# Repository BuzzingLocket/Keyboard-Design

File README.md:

# May 8th 2026 Initial Release 🚀
- 80% keyboard ansi
- Missing a ctrl key on the righthand side
- Uses a Raspberry Pi Pico as the MCU, I was too lazy to implement my own rp2040 MCU design
- Firmware will be updated at a later date
- Everything is designed to be hand soldered
- Printed using a lpkf protomat s103 with traces at 0.4mm, and vias at 0.6mm

# May 14th 2026 Hotfix 🛠️
- lpkf protomat s103 requires vias at 0.8mm diameter with a hole of 0.4mm
- Not the same as 0.6mm diameter with a hole of 0.3mm
- Decided to print with JLCPCB instead of school PCB printer due to costs

# June 2nd 2026 Firmware Release 🚀
- Added QMK firmware
- Full matrix finished
- RGB added
- Could be errors, requires more testing
- QMK uses HSV (hue, saturation, value) not RGB (Red, Green, Blue)

# June 14th 2026 Firmware Update ⚡
- Finalized the QMK firmware
- Edited the rotary encoder resolution from 2 --> 4
- Switched GP21 and GP20 due to preference
- Finished testing keyboard
- Uploaded as .c file

# June 20th 2026 Case Design Release 🚀
- Learned how to use Fusion360
- Created bottom case housing
- Pillars for M2 screws and for support
- 4mm base depth
- 5mm wide walls
- 6mm pillars for pcb to lie on-top
- Designed for M2x4mm (3.5mm width) heat inserts
- Designed for M2x5mm screws
- Uploaded as .STEP and .STL

# June 20th 2026 Firmware Quality of Life ✨
- Uploaded .uf2 file for firmware
- Renamed folders for recognition
- Removed USB C datasheet as it was not used

# August 7th 2026 Keyboard Case Update⚡
- Had to go do some tasks for work so I could not update this for a while
- Went on vacation so long break was taken
- Old keyboard design was not accurate Ie. sides were 5.231mm not 5mm
- Added 1mm tolerance to each edge
- Added holes into the walls
  - Allows for a top portion of the case
      - Higher case level
      - Covers the exposed microcontroller
   
# August 9th 2026 Keyboard Case Update⚡
- Uploaded top case files .stl and .step
- Started the top case design
- Added pillars to insert into sockets from the bottom case
- Added a cover for the Pi Pico

# August 15th 2026 Keyboard Case Update⚡
- Updated bot case files .stl and .step
- Holes were too small as they shrunk when cooled
  - Expanded hole radius by 0.25mm
- Cover for pi pico on 1top case is accurate

# August 25th 2026 Keyboard Print Files Update⚡
- Finished certification and testing of all cases
- Purchasing filament
- Printing at Toronto Metropolitan Universities DME

# September 3rd 2026 Keyboard Print Files Update⚡
- Updated Keyboard print files
- Added a fin onto the back of the Bot_Case to make it print more stable
- Fin helps print diagonally without excessive use of filament from auto generated supports

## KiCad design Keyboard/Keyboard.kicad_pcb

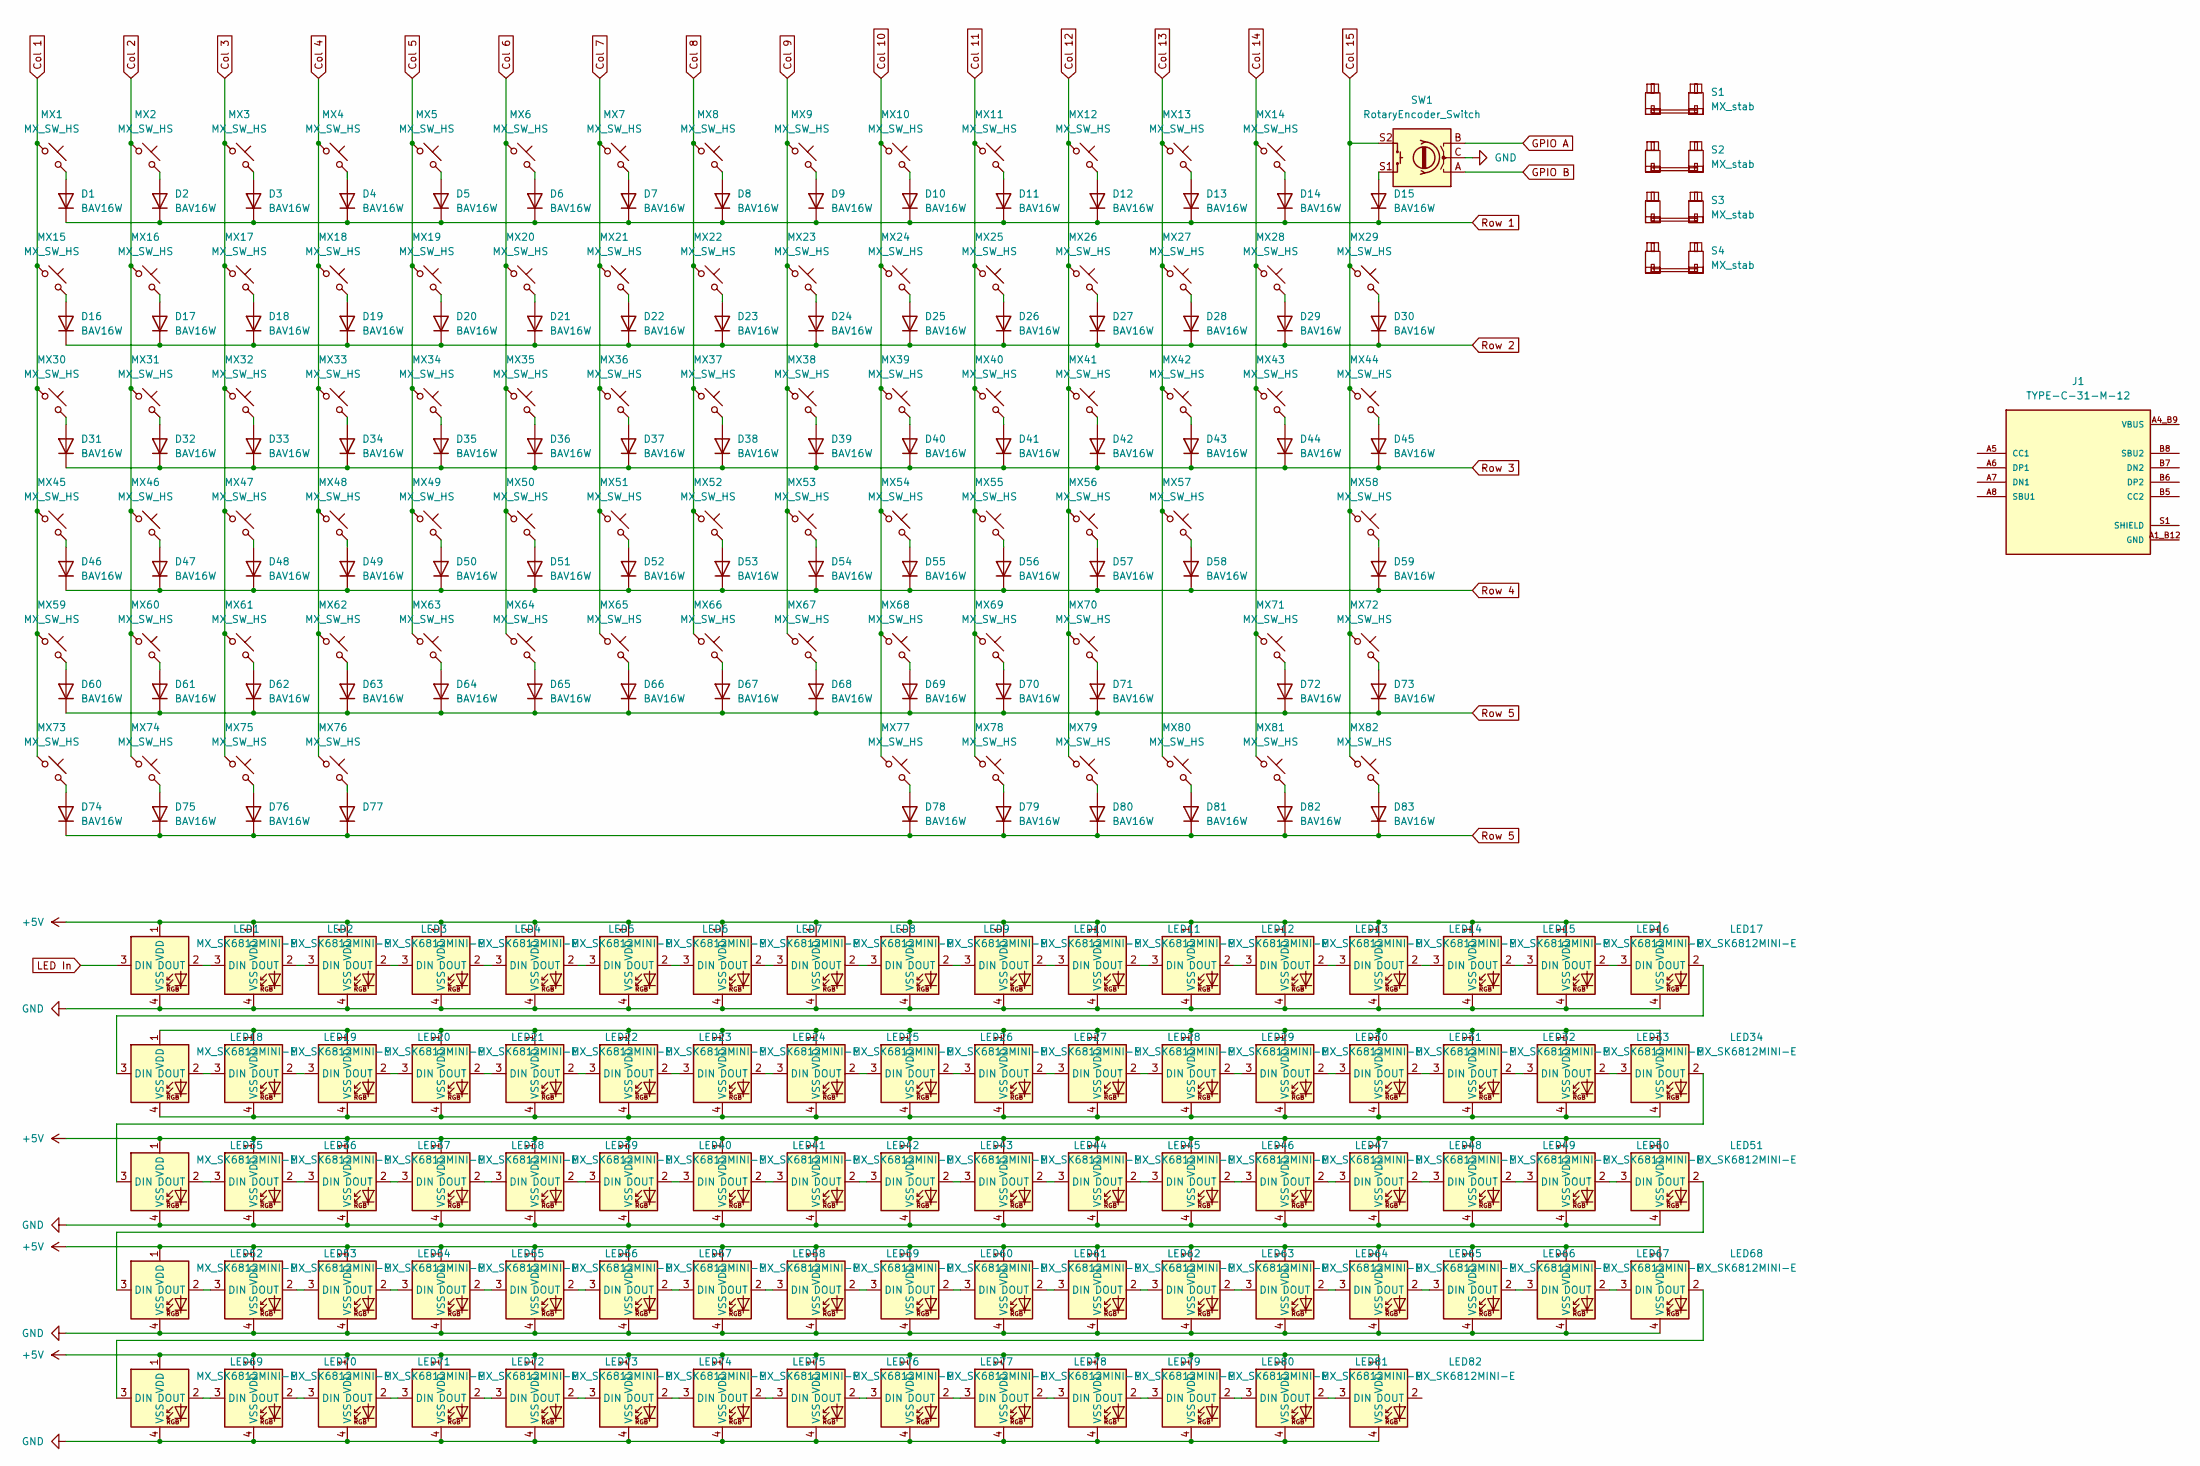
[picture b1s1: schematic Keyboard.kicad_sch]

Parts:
D1, D2, D3, D4, D5, D6, D7, D8, D9, D10, D11, D12, D13, D14, D15, D16, D17, D18, D19, D20, D21, D22, D23, D24, D25, D26, D27, D28, D29, D30, D31, D32, D33, D34, D35, D36, D37, D38, D39, D40, D41, D42, D43, D44, D45, D46, D47, D48, D49, D50, D51, D52, D53, D54, D55, D56, D57, D58, D59, D60, D61, D62, D63, D64, D65, D66, D67, D68, D69, D70, D71, D72, D73, D74, D75, D76, D77, D78, D79, D80, D81, D82, D83: BAV16W; D_SOD-123
J1: TYPE-C-31-M-12; HRO_TYPE-C-31-M-12
LED1, LED2, LED3, LED4, LED5, LED6, LED7, LED8, LED9, LED10, LED11, LED12, LED13, LED14, LED15, LED16, LED17, LED18, LED19, LED20, LED21, LED22, LED23, LED24, LED25, LED26, LED27, LED28, LED29, LED30, LED31, LED32, LED33, LED34, LED35, LED36, LED37, LED38, LED39, LED40, LED41, LED42, LED43, LED44, LED45, LED46, LED47, LED48, LED49, LED50, LED51, LED52, LED53, LED54, LED55, LED56, LED57, LED58, LED59, LED60, LED61, LED62, LED63, LED64, LED65, LED66, LED67, LED68, LED69, LED70, LED71, LED72, LED73, LED74, LED75, LED76, LED77, LED78, LED79, LED80, LED81, LED82: MX_SK6812MINI-E; LED_MX_6028R
MX1, MX2, MX3, MX4, MX5, MX6, MX7, MX8, MX9, MX10, MX11, MX12, MX13, MX14, MX15, MX16, MX17, MX18, MX19, MX20, MX21, MX22, MX23, MX24, MX25, MX26, MX27, MX28, MX29, MX31, MX32, MX33, MX34, MX35, MX36, MX37, MX38, MX39, MX40, MX41, MX42, MX44, MX46, MX47, MX48, MX49, MX50, MX51, MX52, MX53, MX54, MX55, MX56, MX57, MX58, MX59, MX60, MX61, MX62, MX63, MX64, MX65, MX66, MX67, MX68, MX69, MX71, MX72, MX76, MX77, MX78, MX79, MX80, MX81, MX82: MX_SW_HS; SW_MX_HS_CPG151101S11_1u
MX30, MX43: MX_SW_HS; SW_MX_HS_CPG151101S11_1.5u
MX45, MX70: MX_SW_HS; SW_MX_HS_CPG151101S11_1.75u
MX73, MX74, MX75: MX_SW_HS; SW_MX_HS_CPG151101S11_1.25u
S1: MX_stab; STAB_MX_P_2u
S2, S3: MX_stab; STAB_MX_P_2.25u
S4: MX_stab; STAB_MX_P_6.25u
SW1: RotaryEncoder_Switch; RotaryEncoder_Alps_EC11E-Switch_Vertical_H20mm

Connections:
+5V: LED1.1 (VDD), LED2.1 (VDD), LED3.1 (VDD), LED4.1 (VDD), LED5.1 (VDD), LED6.1 (VDD), LED7.1 (VDD), LED8.1 (VDD), LED9.1 (VDD), LED10.1 (VDD), LED11.1 (VDD), LED12.1 (VDD), LED13.1 (VDD), LED14.1 (VDD), LED15.1 (VDD), LED16.1 (VDD), LED17.1 (VDD), LED35.1 (VDD), LED36.1 (VDD), LED37.1 (VDD), LED38.1 (VDD), LED39.1 (VDD), LED40.1 (VDD), LED41.1 (VDD), LED42.1 (VDD), LED43.1 (VDD), LED44.1 (VDD), LED45.1 (VDD), LED46.1 (VDD), LED47.1 (VDD), LED48.1 (VDD), LED49.1 (VDD), LED50.1 (VDD), LED51.1 (VDD), LED52.1 (VDD), LED53.1 (VDD), LED54.1 (VDD), LED55.1 (VDD), LED56.1 (VDD), LED57.1 (VDD), LED58.1 (VDD), LED59.1 (VDD), LED60.1 (VDD), LED61.1 (VDD), LED62.1 (VDD), LED63.1 (VDD), LED64.1 (VDD), LED65.1 (VDD), LED66.1 (VDD), LED67.1 (VDD), LED68.1 (VDD), LED69.1 (VDD), LED70.1 (VDD), LED71.1 (VDD), LED72.1 (VDD), LED73.1 (VDD), LED74.1 (VDD), LED75.1 (VDD), LED76.1 (VDD), LED77.1 (VDD), LED78.1 (VDD), LED79.1 (VDD), LED80.1 (VDD), LED81.1 (VDD), LED82.1 (VDD)
Col 1: MX1.1, MX15.1, MX30.1, MX45.1, MX59.1, MX73.1
Col 2: MX2.1, MX16.1, MX31.1, MX46.1, MX60.1, MX74.1
Col 3: MX3.1, MX17.1, MX32.1, MX47.1, MX61.1, MX75.1
Col 4: MX4.1, MX18.1, MX33.1, MX48.1, MX62.1, MX76.1
Col 5: MX5.1, MX19.1, MX34.1, MX49.1, MX63.1
Col 6: MX6.1, MX20.1, MX35.1, MX50.1, MX64.1
Col 7: MX7.1, MX21.1, MX36.1, MX51.1, MX65.1
Col 8: MX8.1, MX22.1, MX37.1, MX52.1, MX66.1
Col 9: MX9.1, MX23.1, MX38.1, MX53.1, MX67.1
Col 10: MX10.1, MX24.1, MX39.1, MX54.1, MX68.1, MX77.1
Col 11: MX11.1, MX25.1, MX40.1, MX55.1, MX69.1, MX78.1
Col 12: MX12.1, MX26.1, MX41.1, MX56.1, MX70.1, MX79.1
Col 13: MX13.1, MX27.1, MX42.1, MX57.1, MX80.1
Col 14: MX14.1, MX28.1, MX43.1, MX71.1, MX81.1
Col 15: MX29.1, MX44.1, MX58.1, MX72.1, MX82.1, SW1.S2
GND: LED1.4 (VSS), LED2.4 (VSS), LED3.4 (VSS), LED4.4 (VSS), LED5.4 (VSS), LED6.4 (VSS), LED7.4 (VSS), LED8.4 (VSS), LED9.4 (VSS), LED10.4 (VSS), LED11.4 (VSS), LED12.4 (VSS), LED13.4 (VSS), LED14.4 (VSS), LED15.4 (VSS), LED16.4 (VSS), LED17.4 (VSS), LED35.4 (VSS), LED36.4 (VSS), LED37.4 (VSS), LED38.4 (VSS), LED39.4 (VSS), LED40.4 (VSS), LED41.4 (VSS), LED42.4 (VSS), LED43.4 (VSS), LED44.4 (VSS), LED45.4 (VSS), LED46.4 (VSS), LED47.4 (VSS), LED48.4 (VSS), LED49.4 (VSS), LED50.4 (VSS), LED51.4 (VSS), LED52.4 (VSS), LED53.4 (VSS), LED54.4 (VSS), LED55.4 (VSS), LED56.4 (VSS), LED57.4 (VSS), LED58.4 (VSS), LED59.4 (VSS), LED60.4 (VSS), LED61.4 (VSS), LED62.4 (VSS), LED63.4 (VSS), LED64.4 (VSS), LED65.4 (VSS), LED66.4 (VSS), LED67.4 (VSS), LED68.4 (VSS), LED69.4 (VSS), LED70.4 (VSS), LED71.4 (VSS), LED72.4 (VSS), LED73.4 (VSS), LED74.4 (VSS), LED75.4 (VSS), LED76.4 (VSS), LED77.4 (VSS), LED78.4 (VSS), LED79.4 (VSS), LED80.4 (VSS), LED81.4 (VSS), LED82.4 (VSS), SW1.C
GPIO A: SW1.B
GPIO B: SW1.A
LED In: LED1.3 (DIN)
unnamed: D1.2 (A), MX1.2
unnamed: D2.2 (A), MX2.2
unnamed: D3.2 (A), MX3.2
unnamed: D4.2 (A), MX4.2
unnamed: D5.2 (A), MX5.2
unnamed: D6.2 (A), MX6.2
unnamed: D7.2 (A), MX7.2
unnamed: D8.2 (A), MX8.2
unnamed: D9.2 (A), MX9.2
unnamed: D10.2 (A), MX10.2
unnamed: D11.2 (A), MX11.2
unnamed: D12.2 (A), MX12.2
unnamed: D13.2 (A), MX13.2
unnamed: D14.2 (A), MX14.2
unnamed: D15.2 (A), SW1.S1
unnamed: D16.2 (A), MX15.2
unnamed: D17.2 (A), MX16.2
unnamed: D18.2 (A), MX17.2
unnamed: D19.2 (A), MX18.2
unnamed: D20.2 (A), MX19.2
unnamed: D21.2 (A), MX20.2
unnamed: D22.2 (A), MX21.2
unnamed: D23.2 (A), MX22.2
unnamed: D24.2 (A), MX23.2
unnamed: D25.2 (A), MX24.2
unnamed: D26.2 (A), MX25.2
unnamed: D27.2 (A), MX26.2
unnamed: D28.2 (A), MX27.2
unnamed: D29.2 (A), MX28.2
unnamed: D30.2 (A), MX29.2
unnamed: D31.2 (A), MX30.2
unnamed: D32.2 (A), MX31.2
unnamed: D33.2 (A), MX32.2
unnamed: D34.2 (A), MX33.2
unnamed: D35.2 (A), MX34.2
unnamed: D36.2 (A), MX35.2
unnamed: D37.2 (A), MX36.2
unnamed: D38.2 (A), MX37.2
unnamed: D39.2 (A), MX38.2
unnamed: D40.2 (A), MX39.2
unnamed: D41.2 (A), MX40.2
unnamed: D42.2 (A), MX41.2
unnamed: D43.2 (A), MX42.2
unnamed: D44.2 (A), MX43.2
unnamed: D45.2 (A), MX44.2
unnamed: D46.2 (A), MX45.2
unnamed: D47.2 (A), MX46.2
unnamed: D48.2 (A), MX47.2
unnamed: D49.2 (A), MX48.2
unnamed: D50.2 (A), MX49.2
unnamed: D51.2 (A), MX50.2
unnamed: D52.2 (A), MX51.2
unnamed: D53.2 (A), MX52.2
unnamed: D54.2 (A), MX53.2
unnamed: D55.2 (A), MX54.2
unnamed: D56.2 (A), MX55.2
unnamed: D57.2 (A), MX56.2
unnamed: D58.2 (A), MX57.2
unnamed: D59.2 (A), MX58.2
unnamed: D60.2 (A), MX59.2
unnamed: D61.2 (A), MX60.2
unnamed: D62.2 (A), MX61.2
unnamed: D63.2 (A), MX62.2
unnamed: D64.2 (A), MX63.2
unnamed: D65.2 (A), MX64.2
unnamed: D66.2 (A), MX65.2
unnamed: D67.2 (A), MX66.2
unnamed: D68.2 (A), MX67.2
unnamed: D69.2 (A), MX68.2
unnamed: D70.2 (A), MX69.2
unnamed: D71.2 (A), MX70.2
unnamed: D72.2 (A), MX71.2
unnamed: D73.2 (A), MX72.2
unnamed: D74.2 (A), MX73.2
unnamed: D75.2 (A), MX74.2
unnamed: D76.2 (A), MX75.2
unnamed: D77.2 (A), MX76.2
unnamed: D78.2 (A), MX77.2
unnamed: D79.2 (A), MX78.2
unnamed: D80.2 (A), MX79.2
unnamed: D81.2 (A), MX80.2
unnamed: D82.2 (A), MX81.2
unnamed: D83.2 (A), MX82.2
unnamed: J1.A1_B12 (GND), J1.B1_A12 (GND)
unnamed: J1.A4_B9 (VBUS), J1.B4_A9 (VBUS)
unnamed: J1.S1 (SHIELD), J1.S2 (SHIELD), J1.S3 (SHIELD), J1.S4 (SHIELD)
unnamed: LED1.2 (DOUT), LED2.3 (DIN)
unnamed: LED2.2 (DOUT), LED3.3 (DIN)
unnamed: LED3.2 (DOUT), LED4.3 (DIN)
unnamed: LED4.2 (DOUT), LED5.3 (DIN)
unnamed: LED5.2 (DOUT), LED6.3 (DIN)
unnamed: LED6.2 (DOUT), LED7.3 (DIN)
unnamed: LED7.2 (DOUT), LED8.3 (DIN)
unnamed: LED8.2 (DOUT), LED9.3 (DIN)
unnamed: LED9.2 (DOUT), LED10.3 (DIN)
unnamed: LED10.2 (DOUT), LED11.3 (DIN)
unnamed: LED11.2 (DOUT), LED12.3 (DIN)
unnamed: LED12.2 (DOUT), LED13.3 (DIN)
unnamed: LED13.2 (DOUT), LED14.3 (DIN)
unnamed: LED14.2 (DOUT), LED15.3 (DIN)
unnamed: LED15.2 (DOUT), LED16.3 (DIN)
unnamed: LED16.2 (DOUT), LED17.3 (DIN)
unnamed: LED17.2 (DOUT), LED18.3 (DIN)
unnamed: LED18.2 (DOUT), LED19.3 (DIN)
unnamed: LED18.1 (VDD), LED19.1 (VDD), LED20.1 (VDD), LED21.1 (VDD), LED22.1 (VDD), LED23.1 (VDD), LED24.1 (VDD), LED25.1 (VDD), LED26.1 (VDD), LED27.1 (VDD), LED28.1 (VDD), LED29.1 (VDD), LED30.1 (VDD), LED31.1 (VDD), LED32.1 (VDD), LED33.1 (VDD), LED34.1 (VDD)
unnamed: LED18.4 (VSS), LED19.4 (VSS), LED20.4 (VSS), LED21.4 (VSS), LED22.4 (VSS), LED23.4 (VSS), LED24.4 (VSS), LED25.4 (VSS), LED26.4 (VSS), LED27.4 (VSS), LED28.4 (VSS), LED29.4 (VSS), LED30.4 (VSS), LED31.4 (VSS), LED32.4 (VSS), LED33.4 (VSS), LED34.4 (VSS)
unnamed: LED19.2 (DOUT), LED20.3 (DIN)
unnamed: LED20.2 (DOUT), LED21.3 (DIN)
unnamed: LED21.2 (DOUT), LED22.3 (DIN)
unnamed: LED22.2 (DOUT), LED23.3 (DIN)
unnamed: LED23.2 (DOUT), LED24.3 (DIN)
unnamed: LED24.2 (DOUT), LED25.3 (DIN)
unnamed: LED25.2 (DOUT), LED26.3 (DIN)
unnamed: LED26.2 (DOUT), LED27.3 (DIN)
unnamed: LED27.2 (DOUT), LED28.3 (DIN)
unnamed: LED28.2 (DOUT), LED29.3 (DIN)
unnamed: LED29.2 (DOUT), LED30.3 (DIN)
unnamed: LED30.2 (DOUT), LED31.3 (DIN)
unnamed: LED31.2 (DOUT), LED32.3 (DIN)
unnamed: LED32.2 (DOUT), LED33.3 (DIN)
unnamed: LED33.2 (DOUT), LED34.3 (DIN)
unnamed: LED34.2 (DOUT), LED35.3 (DIN)
unnamed: LED35.2 (DOUT), LED36.3 (DIN)
unnamed: LED36.2 (DOUT), LED37.3 (DIN)
unnamed: LED37.2 (DOUT), LED38.3 (DIN)
unnamed: LED38.2 (DOUT), LED39.3 (DIN)
unnamed: LED39.2 (DOUT), LED40.3 (DIN)
unnamed: LED40.2 (DOUT), LED41.3 (DIN)
unnamed: LED41.2 (DOUT), LED42.3 (DIN)
unnamed: LED42.2 (DOUT), LED43.3 (DIN)
unnamed: LED43.2 (DOUT), LED44.3 (DIN)
unnamed: LED44.2 (DOUT), LED45.3 (DIN)
unnamed: LED45.2 (DOUT), LED46.3 (DIN)
unnamed: LED46.2 (DOUT), LED47.3 (DIN)
unnamed: LED47.2 (DOUT), LED48.3 (DIN)
unnamed: LED48.2 (DOUT), LED49.3 (DIN)
unnamed: LED49.2 (DOUT), LED50.3 (DIN)
unnamed: LED50.2 (DOUT), LED51.3 (DIN)
unnamed: LED51.2 (DOUT), LED52.3 (DIN)
unnamed: LED52.2 (DOUT), LED53.3 (DIN)
unnamed: LED53.2 (DOUT), LED54.3 (DIN)
unnamed: LED54.2 (DOUT), LED55.3 (DIN)
unnamed: LED55.2 (DOUT), LED56.3 (DIN)
unnamed: LED56.2 (DOUT), LED57.3 (DIN)
unnamed: LED57.2 (DOUT), LED58.3 (DIN)
unnamed: LED58.2 (DOUT), LED59.3 (DIN)
unnamed: LED59.2 (DOUT), LED60.3 (DIN)
unnamed: LED60.2 (DOUT), LED61.3 (DIN)
unnamed: LED61.2 (DOUT), LED62.3 (DIN)
unnamed: LED62.2 (DOUT), LED63.3 (DIN)
unnamed: LED63.2 (DOUT), LED64.3 (DIN)
unnamed: LED64.2 (DOUT), LED65.3 (DIN)
unnamed: LED65.2 (DOUT), LED66.3 (DIN)
unnamed: LED66.2 (DOUT), LED67.3 (DIN)
unnamed: LED67.2 (DOUT), LED68.3 (DIN)
unnamed: LED68.2 (DOUT), LED69.3 (DIN)
unnamed: LED69.2 (DOUT), LED70.3 (DIN)
unnamed: LED70.2 (DOUT), LED71.3 (DIN)
unnamed: LED71.2 (DOUT), LED72.3 (DIN)
unnamed: LED72.2 (DOUT), LED73.3 (DIN)
unnamed: LED73.2 (DOUT), LED74.3 (DIN)
unnamed: LED74.2 (DOUT), LED75.3 (DIN)
unnamed: LED75.2 (DOUT), LED76.3 (DIN)
unnamed: LED76.2 (DOUT), LED77.3 (DIN)
unnamed: LED77.2 (DOUT), LED78.3 (DIN)
unnamed: LED78.2 (DOUT), LED79.3 (DIN)
unnamed: LED79.2 (DOUT), LED80.3 (DIN)
unnamed: LED80.2 (DOUT), LED81.3 (DIN)
unnamed: LED81.2 (DOUT), LED82.3 (DIN)
Row 1: D1.1 (K), D2.1 (K), D3.1 (K), D4.1 (K), D5.1 (K), D6.1 (K), D7.1 (K), D8.1 (K), D9.1 (K), D10.1 (K), D11.1 (K), D12.1 (K), D13.1 (K), D14.1 (K), D15.1 (K)
Row 2: D16.1 (K), D17.1 (K), D18.1 (K), D19.1 (K), D20.1 (K), D21.1 (K), D22.1 (K), D23.1 (K), D24.1 (K), D25.1 (K), D26.1 (K), D27.1 (K), D28.1 (K), D29.1 (K), D30.1 (K)
Row 3: D31.1 (K), D32.1 (K), D33.1 (K), D34.1 (K), D35.1 (K), D36.1 (K), D37.1 (K), D38.1 (K), D39.1 (K), D40.1 (K), D41.1 (K), D42.1 (K), D43.1 (K), D44.1 (K), D45.1 (K)
Row 4: D46.1 (K), D47.1 (K), D48.1 (K), D49.1 (K), D50.1 (K), D51.1 (K), D52.1 (K), D53.1 (K), D54.1 (K), D55.1 (K), D56.1 (K), D57.1 (K), D58.1 (K), D59.1 (K)
Row 5: D60.1 (K), D61.1 (K), D62.1 (K), D63.1 (K), D64.1 (K), D65.1 (K), D66.1 (K), D67.1 (K), D68.1 (K), D69.1 (K), D70.1 (K), D71.1 (K), D72.1 (K), D73.1 (K), D74.1 (K), D75.1 (K), D76.1 (K), D77.1 (K), D78.1 (K), D79.1 (K), D80.1 (K), D81.1 (K), D82.1 (K), D83.1 (K)

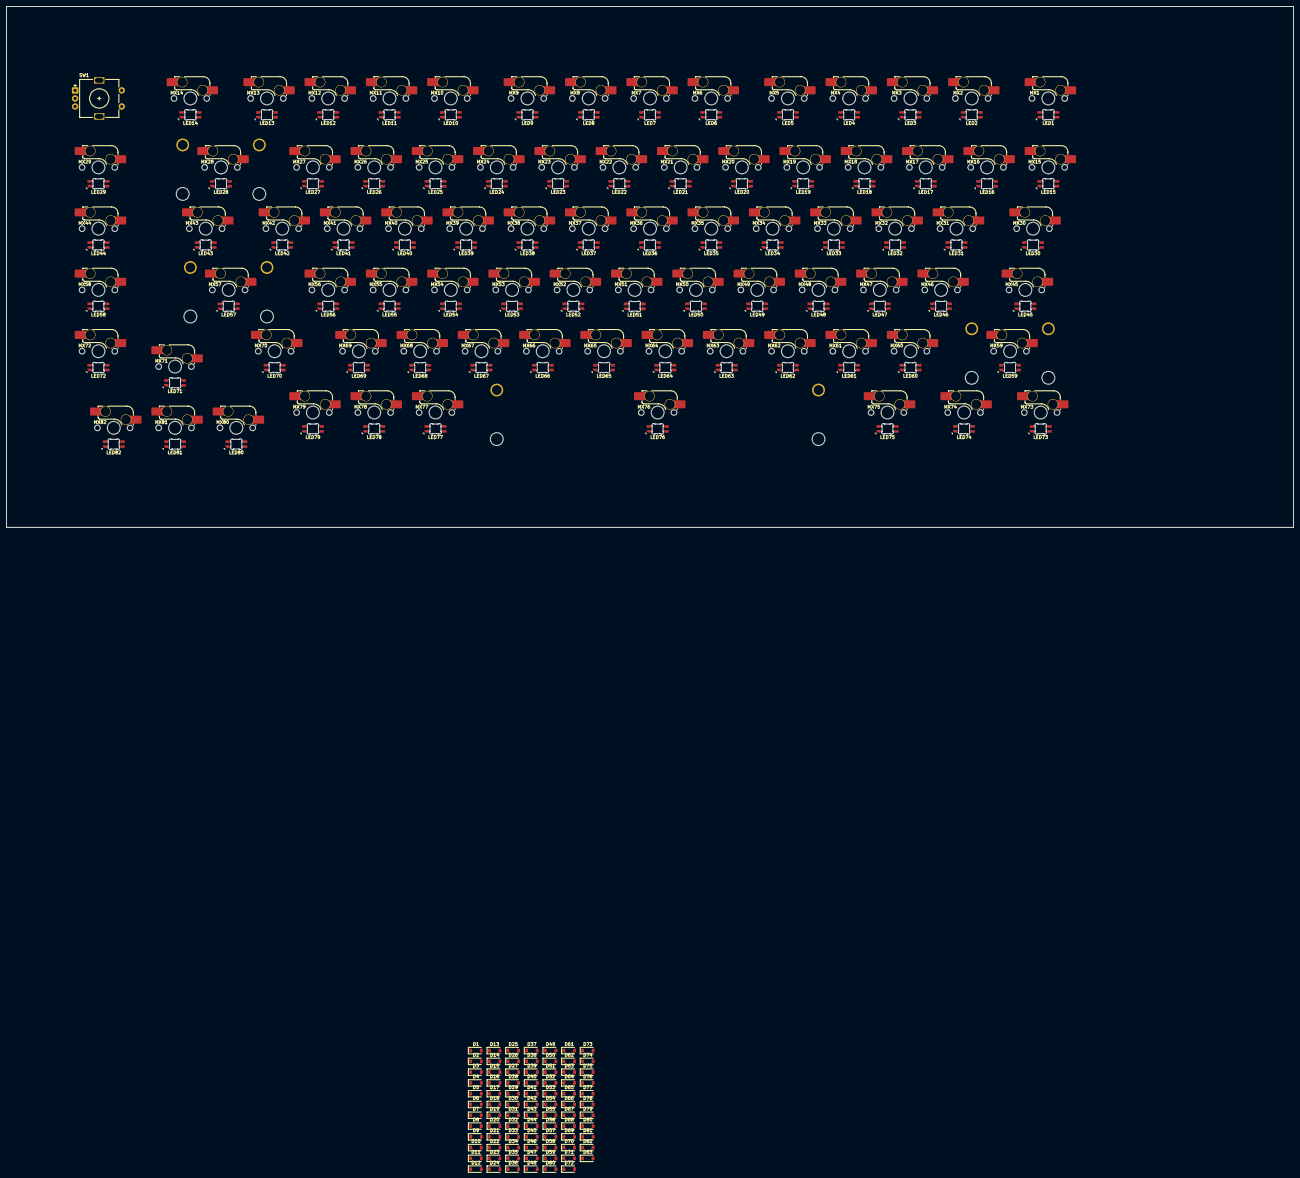
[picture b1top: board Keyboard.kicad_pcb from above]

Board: 2 copper layers, 400.0 x 161.9 mm, 252 parts (0 on the bottom side), 188 nets.

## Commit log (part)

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2026-05-08 Add initial project details to README.md
2026-05-08 Remove outdated firmware update note
    Removed outdated firmware update information.
2026-05-08 Update README with additional design details
2026-06-02 Add files via upload
    Firmware update
2026-06-20 Update README with case design and firmware info
    Added details about case design and firmware updates.
2026-06-20 Rename Keyboard.kicad_pcb to Keyboard.kicad_pcb
2026-06-20 QOL changes
2026-06-20 Organizing project folders
